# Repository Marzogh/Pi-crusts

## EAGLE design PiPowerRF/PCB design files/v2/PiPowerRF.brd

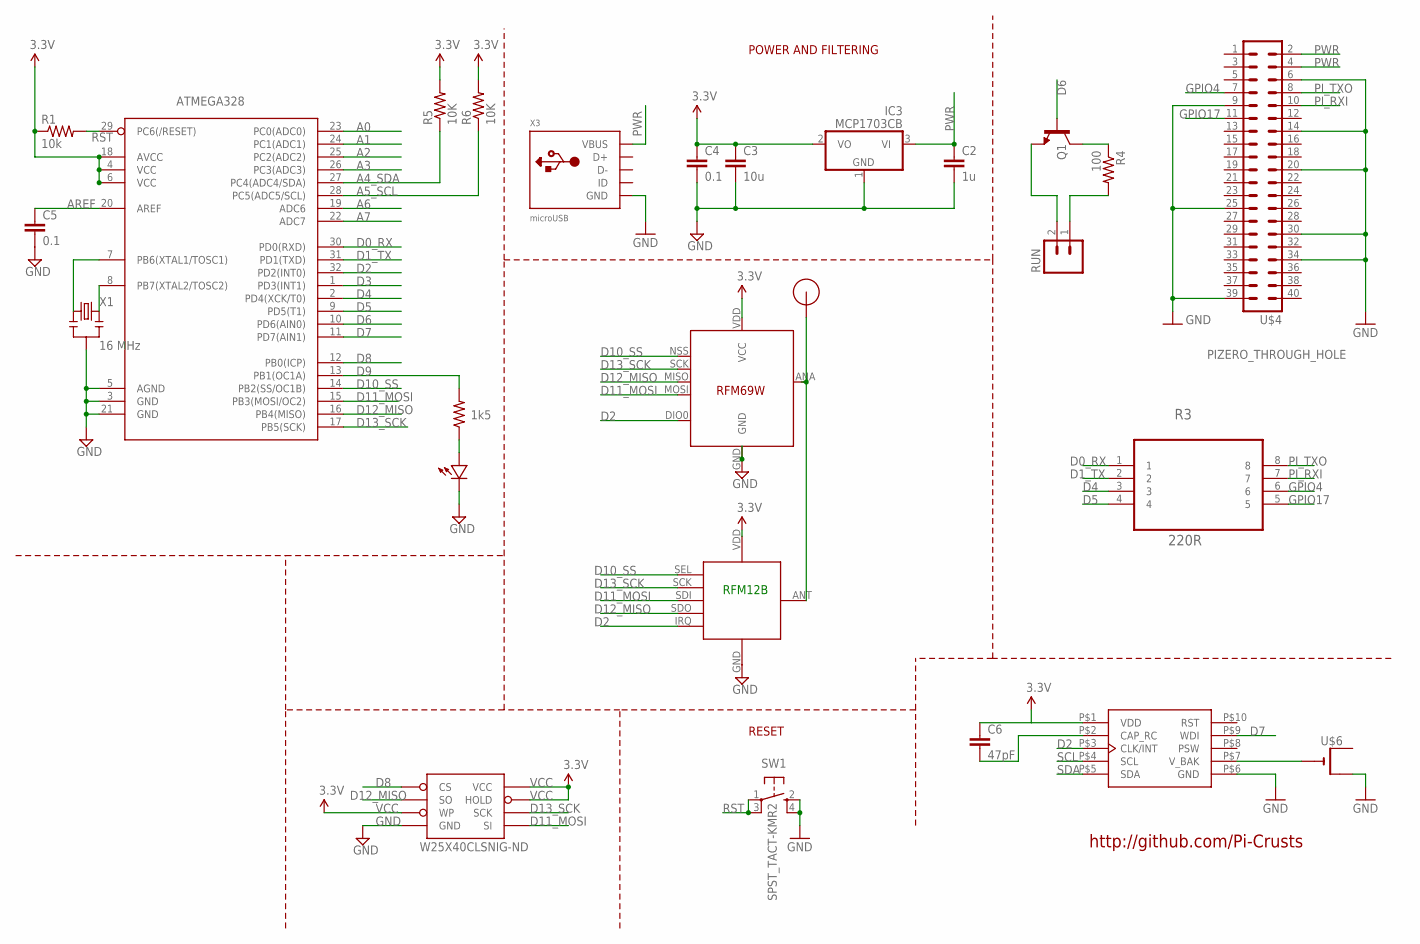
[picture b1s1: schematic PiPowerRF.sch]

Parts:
ATMEGA328: ATMega-328; TQFP32-08
C2: 1u; 0603-CAP
C3: 10u; 0805-CAP
C4, C5: 0.1; 0603-CAP
C6: 47pF; 0402-CAP
IC3: MCP1703CB; SOT23
Q1: MMBT2222A; SOT23-3
R1: 10k; 0603-RES
R2: 1k5; 0603-RES
R3: 220R; RESCAXE80P320X160X60-8N
R4: 100; 0402-RES
R5, R6: 10K; 0603-RES
RFM12B: RFM12B_MINPADS; RFM12B-MINPADS
RUN: M021X02_NO_SILK; 1X02_NO_SILK
SW1: SPST_TACT-KMR2; KMR2
U$1: RFM12B_ANTENNA; RFM12B-ANTENNA
U$2: LED0603; 0603-LED
U$4: PIZERO_THROUGH_HOLE; PIZERO_THOUGH_HOLE
U$5: RFM69; RFM69W-MINPADS
U$6: CR1220SMT; CR1220-SMD
W25X40CLSNIG-ND: AT25F512BWIDE_5.3MM; SO08WIDE
X1: 16 MHz; RESONATOR-SMD
X2: MC-RTC-RV-1805-C3-I2C; MC-RTC-C3
X3: microUSB; 4UCONN_20329_V2

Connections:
A0: ATMEGA328.23 (PC0(ADC0))
A1: ATMEGA328.24 (PC1(ADC1))
A2: ATMEGA328.25 (PC2(ADC2))
A3: ATMEGA328.26 (PC3(ADC3))
A4_SDA: ATMEGA328.27 (PC4(ADC4/SDA)), R5.1
A5_SCL: ATMEGA328.28 (PC5(ADC5/SCL)), R6.1
A6: ATMEGA328.19 (ADC6)
A7: ATMEGA328.22 (ADC7)
AREF: ATMEGA328.20 (AREF), C5.1
D0_RX: ATMEGA328.30 (PD0(RXD)), R3.1
D1_TX: ATMEGA328.31 (PD1(TXD)), R3.2
D2: ATMEGA328.32 (PD2(INT0)), RFM12B.IRQ, U$5.DIO0, X2.P$3 (CLK/INT)
D3: ATMEGA328.1 (PD3(INT1))
D4: ATMEGA328.2 (PD4(XCK/T0)), R3.3
D5: ATMEGA328.9 (PD5(T1)), R3.4
D6: ATMEGA328.10 (PD6(AIN0)), Q1.1 (B)
D7: ATMEGA328.11 (PD7(AIN1)), X2.P$9 (WDI)
D8: ATMEGA328.12 (PB0(ICP)), W25X40CLSNIG-ND.1 (CS)
D9: ATMEGA328.13 (PB1(OC1A)), R2.2
D10_SS: ATMEGA328.14 (PB2(SS/OC1B)), RFM12B.SEL, U$5.NSS (SEL)
D11_MOSI: ATMEGA328.15 (PB3(MOSI/OC2)), RFM12B.SDI (SDI/MOSI), U$5.MOSI, W25X40CLSNIG-ND.5 (SI)
D12_MISO: ATMEGA328.16 (PB4(MISO)), RFM12B.SDO (SDO/MISO), U$5.MISO, W25X40CLSNIG-ND.2 (SO)
D13_SCK: ATMEGA328.17 (PB5(SCK)), RFM12B.SCK, U$5.SCK, W25X40CLSNIG-ND.6 (SCK)
GND: ATMEGA328.3 (GND), ATMEGA328.5 (AGND), ATMEGA328.21 (GND), C2.2, C3.2, C4.2, C5.2, IC3.1 (GND), RFM12B.GND, SW1.2 (S), SW1.4 (S1), U$2.MINUS, U$4.6, U$4.9, U$4.14, U$4.20, U$4.25, U$4.30, U$4.34, U$4.39, U$5.GND, U$6.+$2 (+1), W25X40CLSNIG-ND.4 (GND), X1.2, X2.P$6 (GND), X3.BASE@1 (GND), X3.BASE@2 (GND), X3.GND, X3.SPRT@1 (GND), X3.SPRT@2 (GND), X3.SPRT@3 (GND), X3.SPRT@4 (GND)
GPIO4: R3.6, U$4.7
GPIO17: R3.5, U$4.11
unnamed: ATMEGA328.7 (PB6(XTAL1/TOSC1)), X1.1
unnamed: R2.1, U$2.PLUS
unnamed: RFM12B.ANT, U$1.P$1, U$5.ANA (ANT)
unnamed: R4.2, RUN.1
unnamed: Q1.2 (E), RUN.2
unnamed: U$6.-, X2.P$7 (V_BAK)
unnamed: Q1.3 (C), R4.1
unnamed: C6.2, X2.P$2 (CAP_RC)
unnamed: ATMEGA328.8 (PB7(XTAL2/TOSC2)), X1.3
PI_RXI: R3.7, U$4.10
PI_TXO: R3.8, U$4.8
PWR: C2.1, IC3.3 (VI), U$4.2, U$4.4, X3.VBUS
RST: ATMEGA328.29 (PC6(/RESET)), R1.2, SW1.1, SW1.3 (P1)
SCL: X2.P$4 (SCL)
SDA: X2.P$5 (SDA)
VCC: ATMEGA328.4 (VCC), ATMEGA328.6 (VCC), ATMEGA328.18 (AVCC), C3.1, C4.1, C6.1, IC3.2 (VO), R1.1, R5.2, R6.2, RFM12B.VDD, U$5.VDD (VCC), W25X40CLSNIG-ND.3 (WP), W25X40CLSNIG-ND.7 (HOLD), W25X40CLSNIG-ND.8 (VCC), X2.P$1 (VDD)

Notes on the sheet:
http://github.com/Pi-Crusts
RFM12B
POWER AND FILTERING
RESET

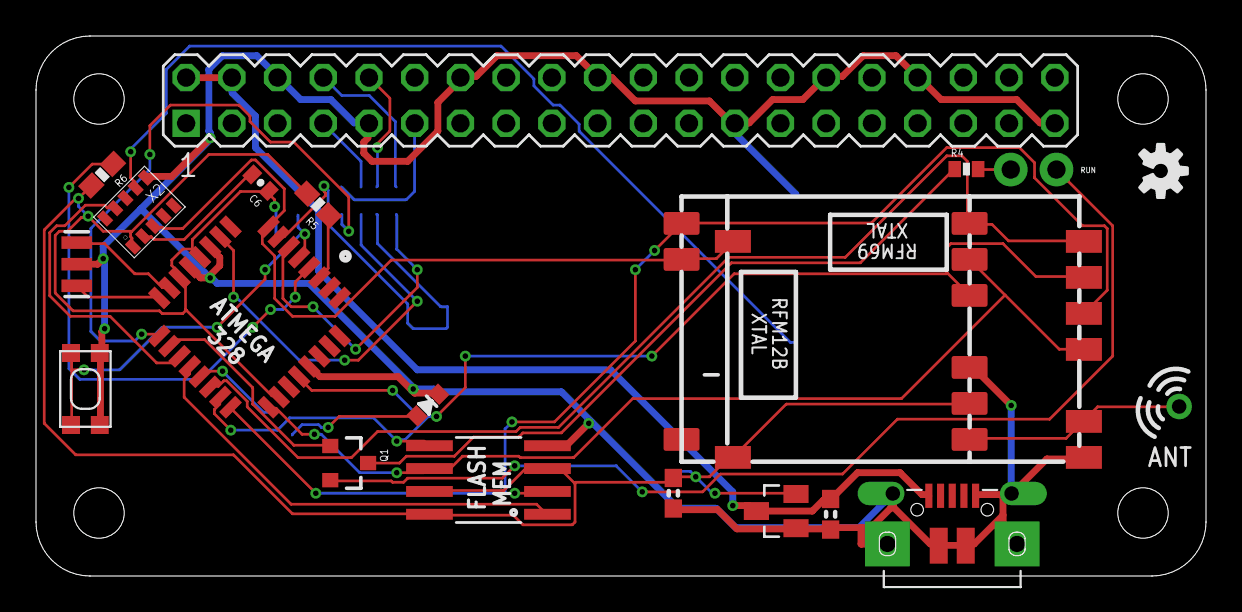
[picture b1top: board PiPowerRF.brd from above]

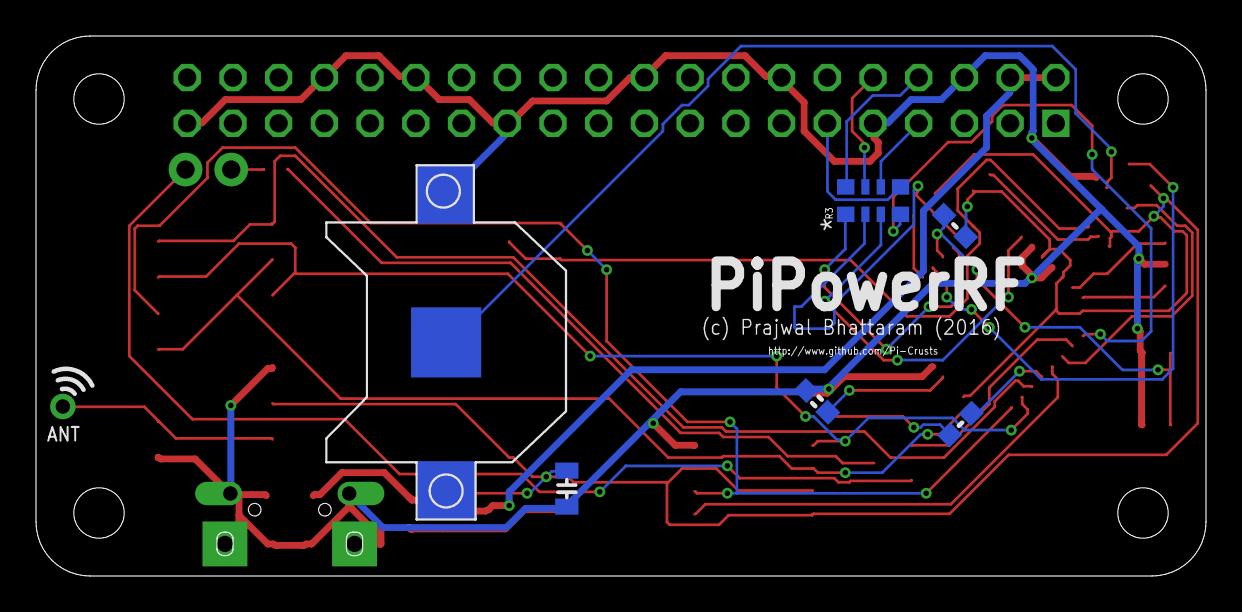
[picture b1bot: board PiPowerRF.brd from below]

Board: 2 copper layers, 65.0 x 30.0 mm, 27 parts (7 on the bottom side), 33 nets.

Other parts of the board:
U$3: OSHW-LOGO-S

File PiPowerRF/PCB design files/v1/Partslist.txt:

Partlist

Exported from PiPowerRF.sch at 16/03/2016 9:09 AM

EAGLE Version 7.2.0 Copyright (c) 1988-2014 CadSoft

Assembly variant: 

Part            Value                 Device                  Package                 Library               Sheet

ATMEGA328       ATMega-328            ATMEGA168/328TQFP32     TQFP32-08               LowPowerLab           1
C1              0.1                   CAP0603-CAP             0603-CAP                LowPowerLab           1
C2              1u                    CAP0603-CAP             0603-CAP                LowPowerLab           1
C3              10u                   CAP0805-CAP             0805-CAP                LowPowerLab           1
C4              0.1                   CAP0603-CAP             0603-CAP                LowPowerLab           1
C5              0.1                   CAP0603-CAP             0603-CAP                LowPowerLab           1
C6              47pF                  CAP0402-CAP             0402-CAP                SparkFun-Capacitors   1
FTDI            FTDI                  M06SIP                  1X06                    SparkFun-Connectors   1
IC3             MCP1703CB             MCP1703CB               SOT23                   linear                1
J1              AVR_SPI_PRG_6PTH      AVR_SPI_PRG_6PTH        2X3                     SparkFun-Connectors   1
Q1              MMBT2222A             TRANSISTOR_NPNMMBT2222A SOT23-3                 SparkFun-DiscreteSemi 1
R1              10k                   RESISTOR0603-RES        0603-RES                LowPowerLab           1
R2              1k5                   RESISTOR0603-RES        0603-RES                LowPowerLab           1
R3               220R                 EXB38V221JV             RESCAXE80P320X160X60-8N Panasonic-EXB-ERJ     1
R4              100                   RESISTOR0402-RES        0402-RES                SparkFun-Passives     1
R5              10K                   RESISTOR0603            0603-RES                SparkFun-Resistors    1
R6              10K                   RESISTOR0603            0603-RES                SparkFun-Resistors    1
RFM12B          RFM12B_MINPADS        RFM12B_MINPADS          RFM12B-MINPADS          LowPowerLab           1
RUN                                   M021X02_NO_SILK         1X02_NO_SILK            SparkFun-Connectors   1
SW1             SPST_TACT-KMR2        SPST_TACT-KMR2          KMR2                    adafruit              1
U$1             RFM12B_ANTENNA        RFM12B_ANTENNA          RFM12B-ANTENNA          LowPowerLab           1
U$2             LED0603               LED0603                 0603-LED                LowPowerLab           1
U$4             PIZERO_THROUGH_HOLE   PIZERO_THROUGH_HOLE     PIZERO_THOUGH_HOLE      pizero                1
U$5             RFM69                 RFM69                   RFM69W-MINPADS          LowPowerLab           1
U$6                                   CR1220SMT               CR1220-SMD              adafruit              1
W25X40CLSNIG-ND AT25F512BWIDE_5.3MM   AT25F512BWIDE_5.3MM     SO08WIDE                LowPowerLab           1
X1              16 MHz                RESONATORSMD            RESONATOR-SMD           SparkFun              1
X2              MC-RTC-RV-1805-C3-I2C MC-RTC-RV-1805-C3-I2C   MC-RTC-C3               Microcrystal-RTC      1
X3              microUSB              USB_MICRO_20329_V2      4UCONN_20329_V2         microbuilder          1

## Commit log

2016-03-15 V1.0 of PiPowerRF
2016-03-15 Added .gitignore
2016-03-15 Added PiMonitorRF
2016-03-15 Updated Gerbers and partlist
2016-03-16 cleanup and sort
2016-03-16 Fixed unexpected airwires
2016-03-22 Added gitignore and License
2016-04-07 v2 ofPiPowerRF added
2016-04-07 v2 ofPiPowerRF silkscreen fixed
2016-04-07 v2 Seeed studio gerbers added

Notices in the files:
parts and their libraries:
SparkFun-Connectors: Licensing: CC v3.0 Share-Alike You are welcome to use this library for commercial purposes.
microbuilder: This work is placed in the public domain, and may be freely used for commercial and non-commercial work with the following conditions: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
